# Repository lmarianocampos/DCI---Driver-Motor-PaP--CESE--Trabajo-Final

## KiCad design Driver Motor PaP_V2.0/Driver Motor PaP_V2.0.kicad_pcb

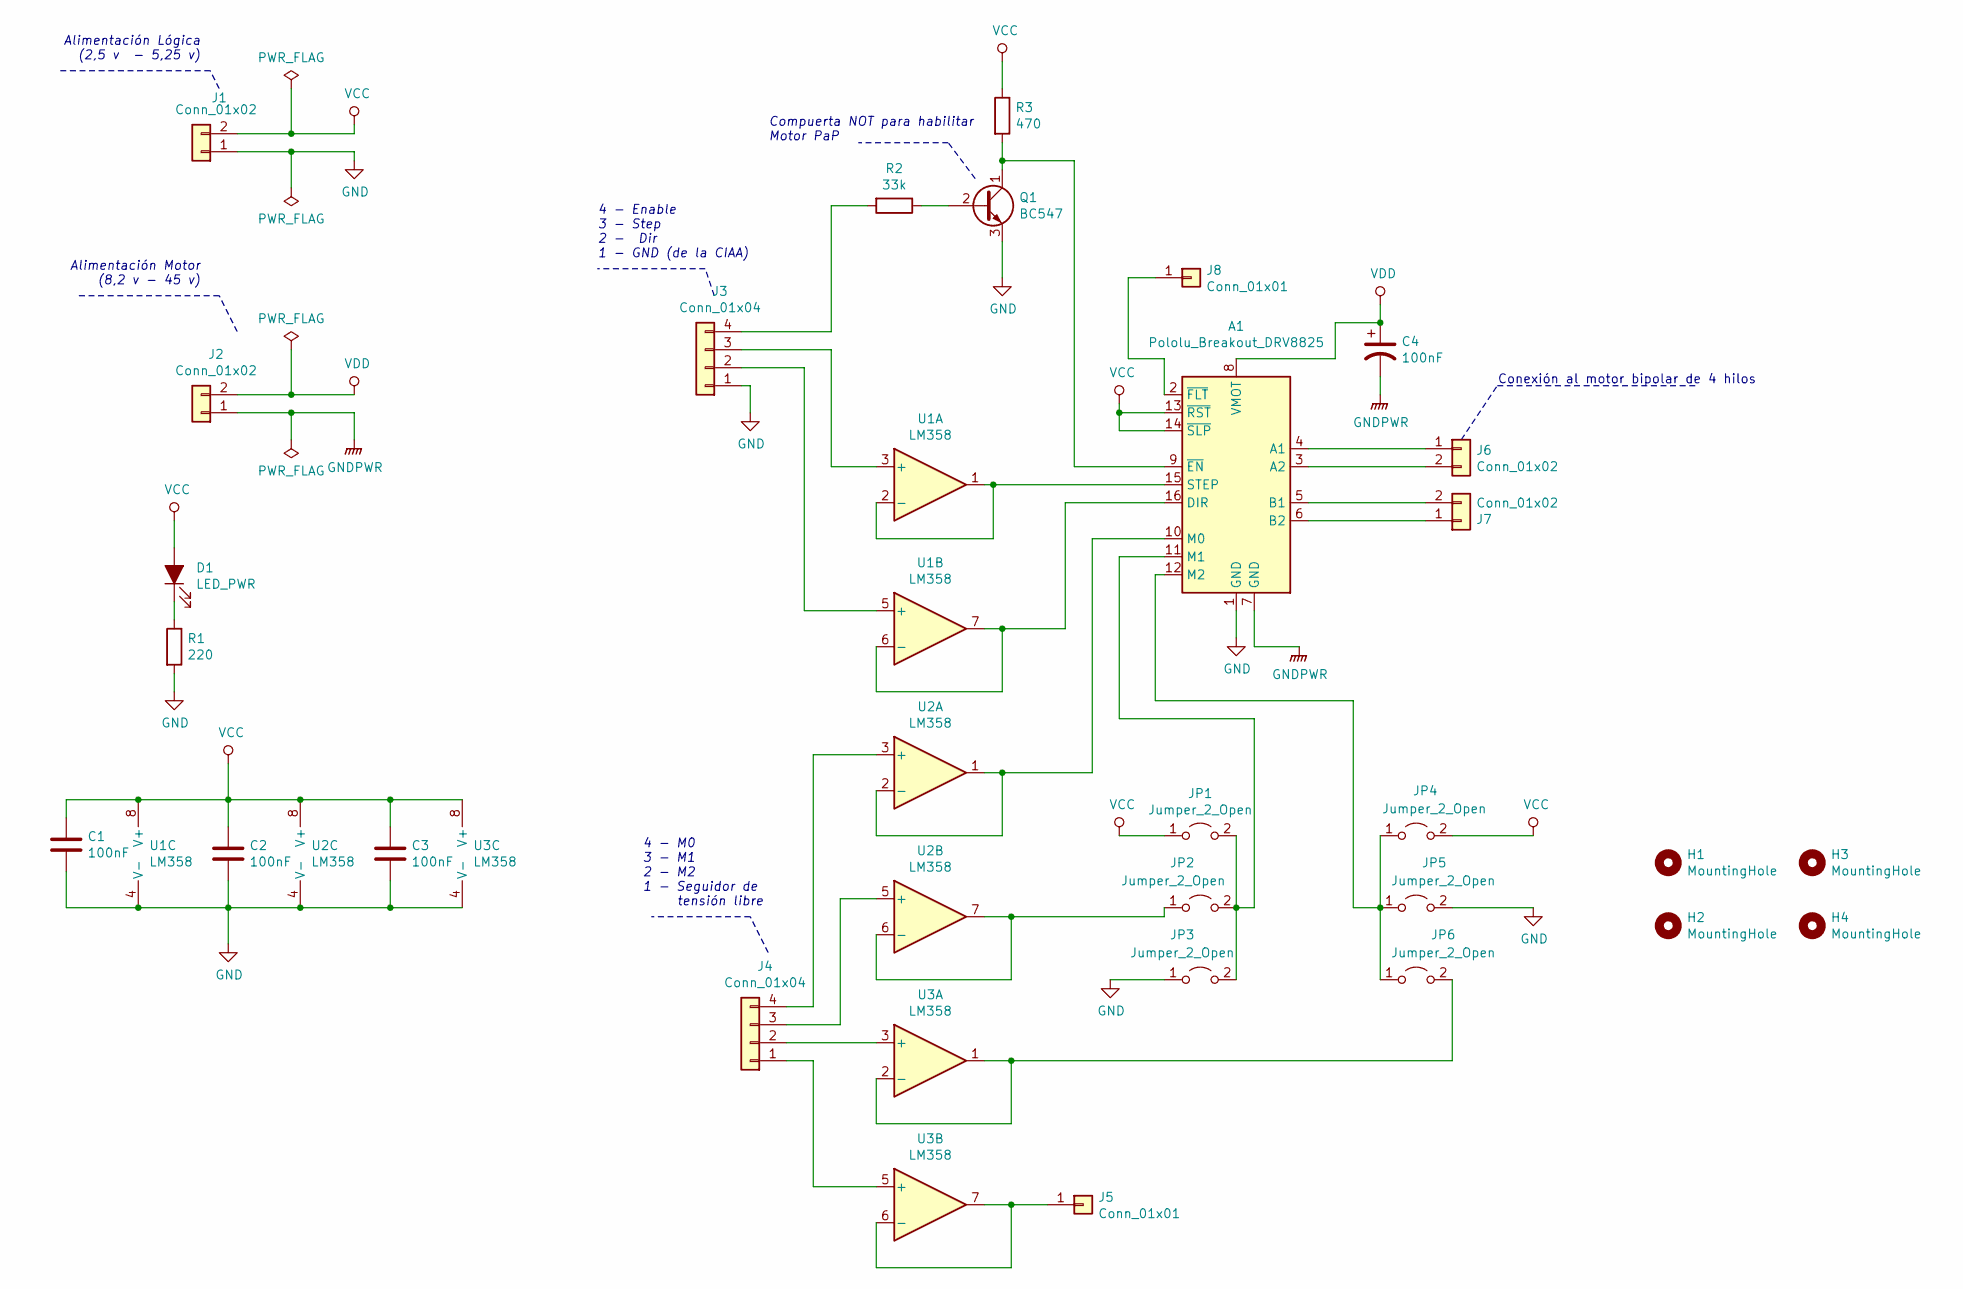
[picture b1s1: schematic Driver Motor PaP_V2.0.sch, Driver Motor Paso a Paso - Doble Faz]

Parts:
A1: Pololu_Breakout_DRV8825; Pololu_Breakout-16_15.2x20.3mm
C1, C2, C3: 100nF; C_Disc_D4.3mm_W1.9mm_P5.00mm
C4: 100nF; CP_Radial_D6.3mm_P2.50mm
D1: LED_PWR; LED_D5.0mm
H1, H2, H3, H4: MountingHole; MountingHole_4mm_Pad_Via
J1, J2: Conn_01x02; TerminalBlock_Phoenix_MKDS-1,5-2-5.08_1x02_P5.08mm_Horizont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
J3, J4: Conn_01x04; Molex_KK-254_AE-6410-04A_1x04_P2.54mm_Vertical
J5, J8: Conn_01x01; PinHeader_1x01_P2.54mm_Vertical
J6, J7: Conn_01x02; Molex_KK-254_AE-6410-02A_1x02_P2.54mm_Vertical
JP1, JP2, JP3, JP4, JP5, JP6: Jumper_2_Open; PinHeader_1x02_P2.54mm_Vertical
Q1: BC547; TO-92_Inline
R1: 220; R_Axial_DIN0207_L6.3mm_D2.5mm_P10.16mm_Horizontal
R2: 33k; R_Axial_DIN0207_L6.3mm_D2.5mm_P10.16mm_Horizontal
R3: 470; R_Axial_DIN0207_L6.3mm_D2.5mm_P10.16mm_Horizontal
U1, U2, U3: LM358; DIP-8_W7.62mm_Socket

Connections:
GND: A1.1 (GND), C1.2, C2.2, C3.2, J1.1, J3.1, JP3.1 (A), JP5.2 (B), Q1.3 (E), R1.2, U1.4 (V-), U2.4 (V-), U3.4 (V-)
GNDPWR: A1.7 (GND), C4.2, J2.1
unnamed: A1.2 (~FLT), J8.1
unnamed: A1.3 (A2), J6.2
unnamed: A1.4 (A1), J6.1
unnamed: A1.5 (B1), J7.2
unnamed: A1.6 (B2), J7.1
unnamed: A1.9 (~EN), Q1.1 (C), R3.2
unnamed: A1.10 (M0), U2.1, U2.2 (-)
unnamed: A1.11 (M1), JP1.2 (B), JP2.2 (B), JP3.2 (B)
unnamed: A1.12 (M2), JP4.1 (A), JP5.1 (A), JP6.1 (A)
unnamed: A1.15 (STEP), U1.1, U1.2 (-)
unnamed: A1.16 (DIR), U1.6 (-), U1.7
unnamed: D1.1 (K), R1.1
unnamed: J3.2, U1.5 (+)
unnamed: J3.3, U1.3 (+)
unnamed: J3.4, R2.2
unnamed: J4.1, U3.5 (+)
unnamed: J4.2, U3.3 (+)
unnamed: J4.3, U2.5 (+)
unnamed: J4.4, U2.3 (+)
unnamed: J5.1, U3.6 (-), U3.7
unnamed: JP2.1 (A), U2.6 (-), U2.7
unnamed: JP6.2 (B), U3.1, U3.2 (-)
unnamed: Q1.2 (B), R2.1
VCC: A1.13 (~RST), A1.14 (~SLP), C1.1, C2.1, C3.1, D1.2 (A), J1.2, JP1.1 (A), JP4.2 (B), R3.1, U1.8 (V+), U2.8 (V+), U3.8 (V+)
VDD: A1.8 (VMOT), C4.1, J2.2

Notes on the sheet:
Alimentación Lógica (2,5 v - 5,25 v)
Alimentación Motor (8,2 v - 45 v)
Compuerta NOT para habilitar Motor PaP
4 - Enable 3 - Step 2 - Dir 1 - GND (de la CIAA)
4 - M0 3 - M1 2 - M2 1 - Seguidor de tensión libre
Conexión al motor bipolar de 4 hilos

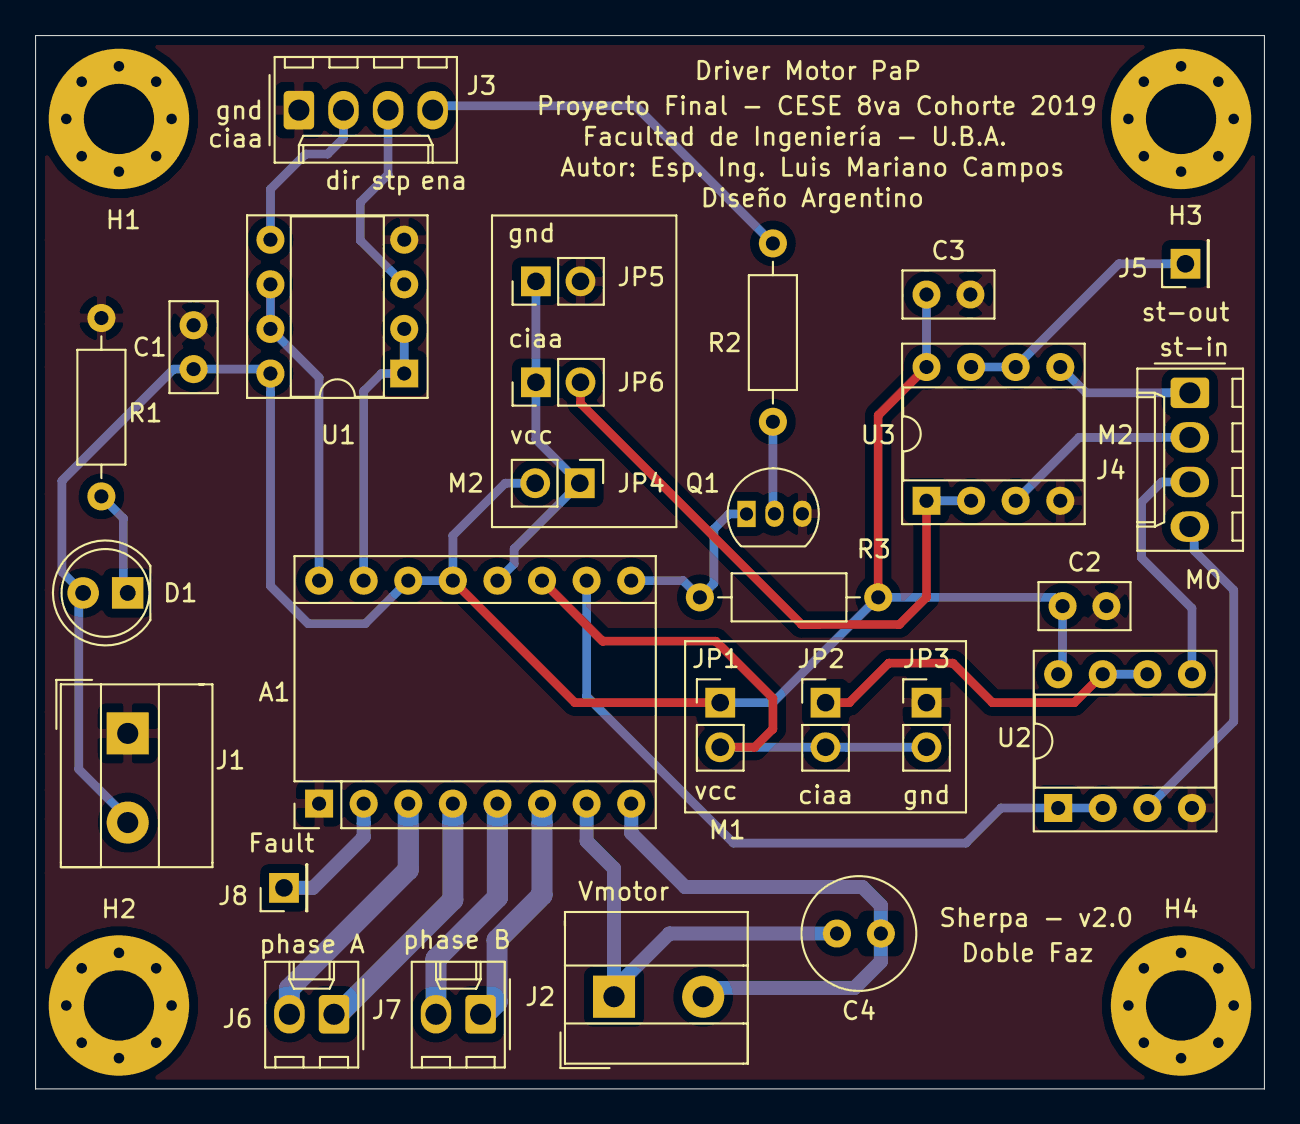
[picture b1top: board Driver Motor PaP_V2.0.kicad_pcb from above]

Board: 2 copper layers, 70.0 x 60.0 mm, 31 parts (0 on the bottom side), 27 nets.

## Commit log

2020-05-18 inciando el diseño en esquematico
2020-05-19 se empezo agregar footprints y continuar
2020-05-20 esquematico Finalizado e iniciando el ruteo en el PCB
2020-05-21 Finalizado el ruteo. Revisar nuevamente
2020-05-24 PCB FInalizadoy con BOM, realizar una última verificación
2020-06-02 Cambiando y creando nuevo Footprints y modelos 3D
2020-06-02 generación de archivos gerber y archivos de tealadrados
